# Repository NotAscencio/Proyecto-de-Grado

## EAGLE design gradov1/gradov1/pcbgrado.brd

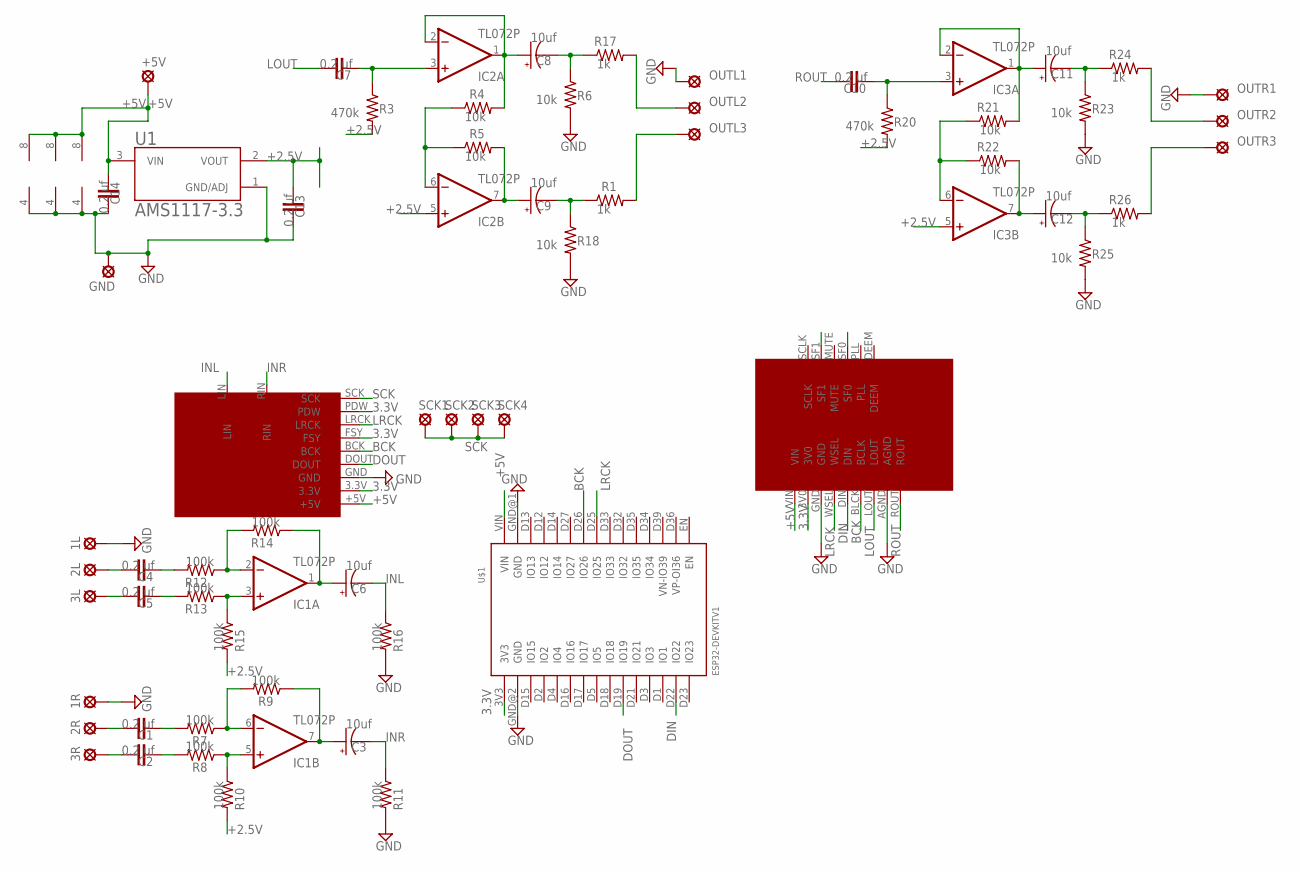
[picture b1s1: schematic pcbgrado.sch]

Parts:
1L, 1R, 2L, 2R, 3L, 3R: LSP10
+5V: LSP10
C1, C2, C4, C5, C13, C14: C-EU025-025X050; C025-025X050
C3, C6, C8, C9, C11, C12: CPOL-USE1.8-4; E1,8-4
C7, C10: C-EU025-030X050; C025-030X050
GND: LSP10
IC1, IC2, IC3: TL072P; DIL08
OUTL1, OUTL2, OUTL3: LSP10
OUTR1, OUTR2, OUTR3: LSP10
R1, R3, R4, R5, R6, R7, R8, R9, R10, R11, R12, R13, R14, R15, R16, R17, R18, R20, R21, R22, R23, R24, R25, R26: R-US_0204/7; 0204/7
SCK1, SCK2, SCK3, SCK4: LSP10
U1: AMS1117-3.3; SOT229P700X180-4N
U$1: ESP32DEVKITV1; ESP32-DEVKITV1
U$2: PCM1802DIS; PCM1802PC
U$3: UDA1334A

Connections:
1: C10.2, IC3.3 (+IN), R20.1
2: C7.2, IC2.3 (+IN), R3.1
3.3V: U$1.3V3, U$2.3.3V, U$2.FSY, U$2.PDW, U$3.3V0
+2.5V: C13.2, IC2.5 (+IN), IC3.5 (+IN), R3.2, R10.2, R15.2, R20.2, U1.2 (VOUT)
+5V: +5V.MP, C14.2, IC1.8 (V+), IC2.8 (V+), IC3.8 (V+), U1.3 (VIN), U$1.VIN, U$2.+5V, U$3.VIN
BCK: U$1.D26 (IO26), U$2.BCK, U$3.BLCK (BCLK)
DIN: U$1.D22 (IO22), U$3.DIN
DOUT: U$1.D19 (IO19), U$2.DOUT
GND: 1L.MP, 1R.MP, C13.1, C14.1, GND.MP, IC1.4 (V-), IC2.4 (V-), IC3.4 (V-), OUTL1.MP, OUTR1.MP, R6.2, R11.2, R16.2, R18.2, R23.2, R25.2, U1.1 (GND/ADJ), U$1.GND@1 (GND), U$1.GND@2 (GND), U$2.GND, U$3.AGND, U$3.GND
INL: C6.-, R16.1, U$2.LIN
INR: C3.-, R11.1, U$2.RIN
LOUT: C7.1, U$3.LOUT
LRCK: U$1.D25 (IO25), U$2.LRCK, U$3.WSEL
unnamed: 2L.MP, C4.1
unnamed: 3L.MP, C5.1
unnamed: 2R.MP, C1.1
unnamed: C1.2, R7.2
unnamed: IC2.6 (-IN), R4.1, R5.1
unnamed: C8.+, IC2.1 (OUT), IC2.2 (-IN), R4.2
unnamed: C9.+, IC2.7 (OUT), R5.2
unnamed: C8.-, R6.1, R17.1
unnamed: 3R.MP, C2.1
unnamed: C2.2, R8.2
unnamed: IC1.6 (-IN), R7.1, R9.2
unnamed: IC1.5 (+IN), R8.1, R10.1
unnamed: C3.+, IC1.7 (OUT), R9.1
unnamed: C5.2, R13.2
unnamed: C4.2, R12.2
unnamed: IC1.3 (+IN), R13.1, R15.1
unnamed: IC1.2 (-IN), R12.1, R14.2
unnamed: C6.+, IC1.1 (OUT), R14.1
unnamed: OUTL2.MP, R17.2
unnamed: C9.-, R1.1, R18.1
unnamed: OUTL3.MP, R1.2
unnamed: C11.+, IC3.1 (OUT), IC3.2 (-IN), R21.2
unnamed: IC3.6 (-IN), R21.1, R22.1
unnamed: C12.+, IC3.7 (OUT), R22.2
unnamed: C11.-, R23.1, R24.1
unnamed: OUTR2.MP, R24.2
unnamed: C12.-, R25.1, R26.1
unnamed: OUTR3.MP, R26.2
ROUT: C10.1, U$3.ROUT
SCK: SCK1.MP, SCK2.MP, SCK3.MP, SCK4.MP, U$2.SCK

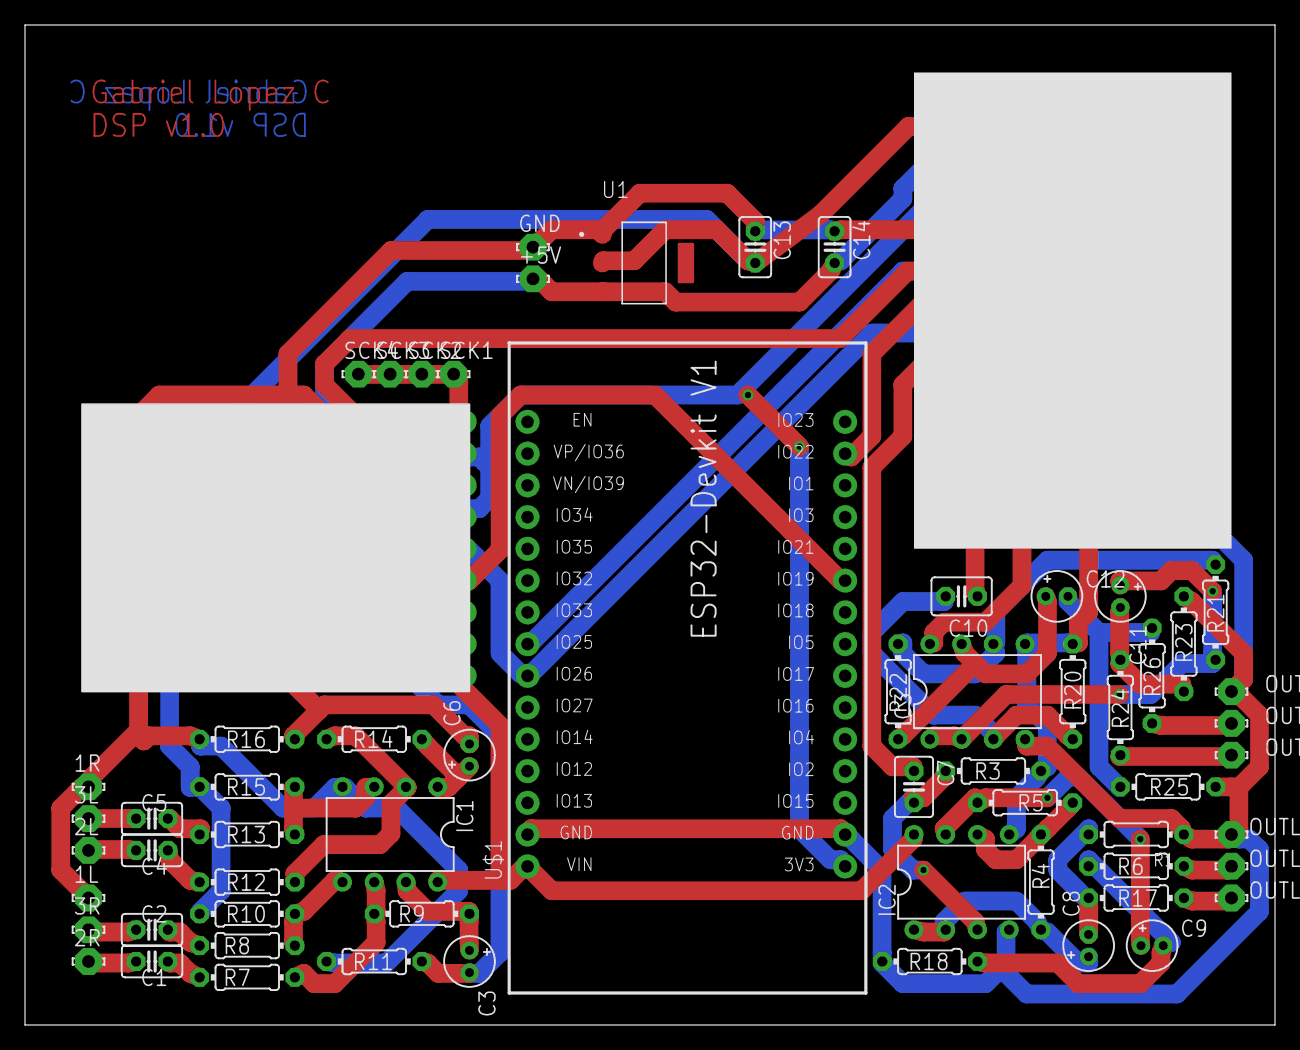
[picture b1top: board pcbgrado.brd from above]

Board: 2 copper layers, 100.0 x 80.0 mm, 63 parts (0 on the bottom side), 43 nets.
